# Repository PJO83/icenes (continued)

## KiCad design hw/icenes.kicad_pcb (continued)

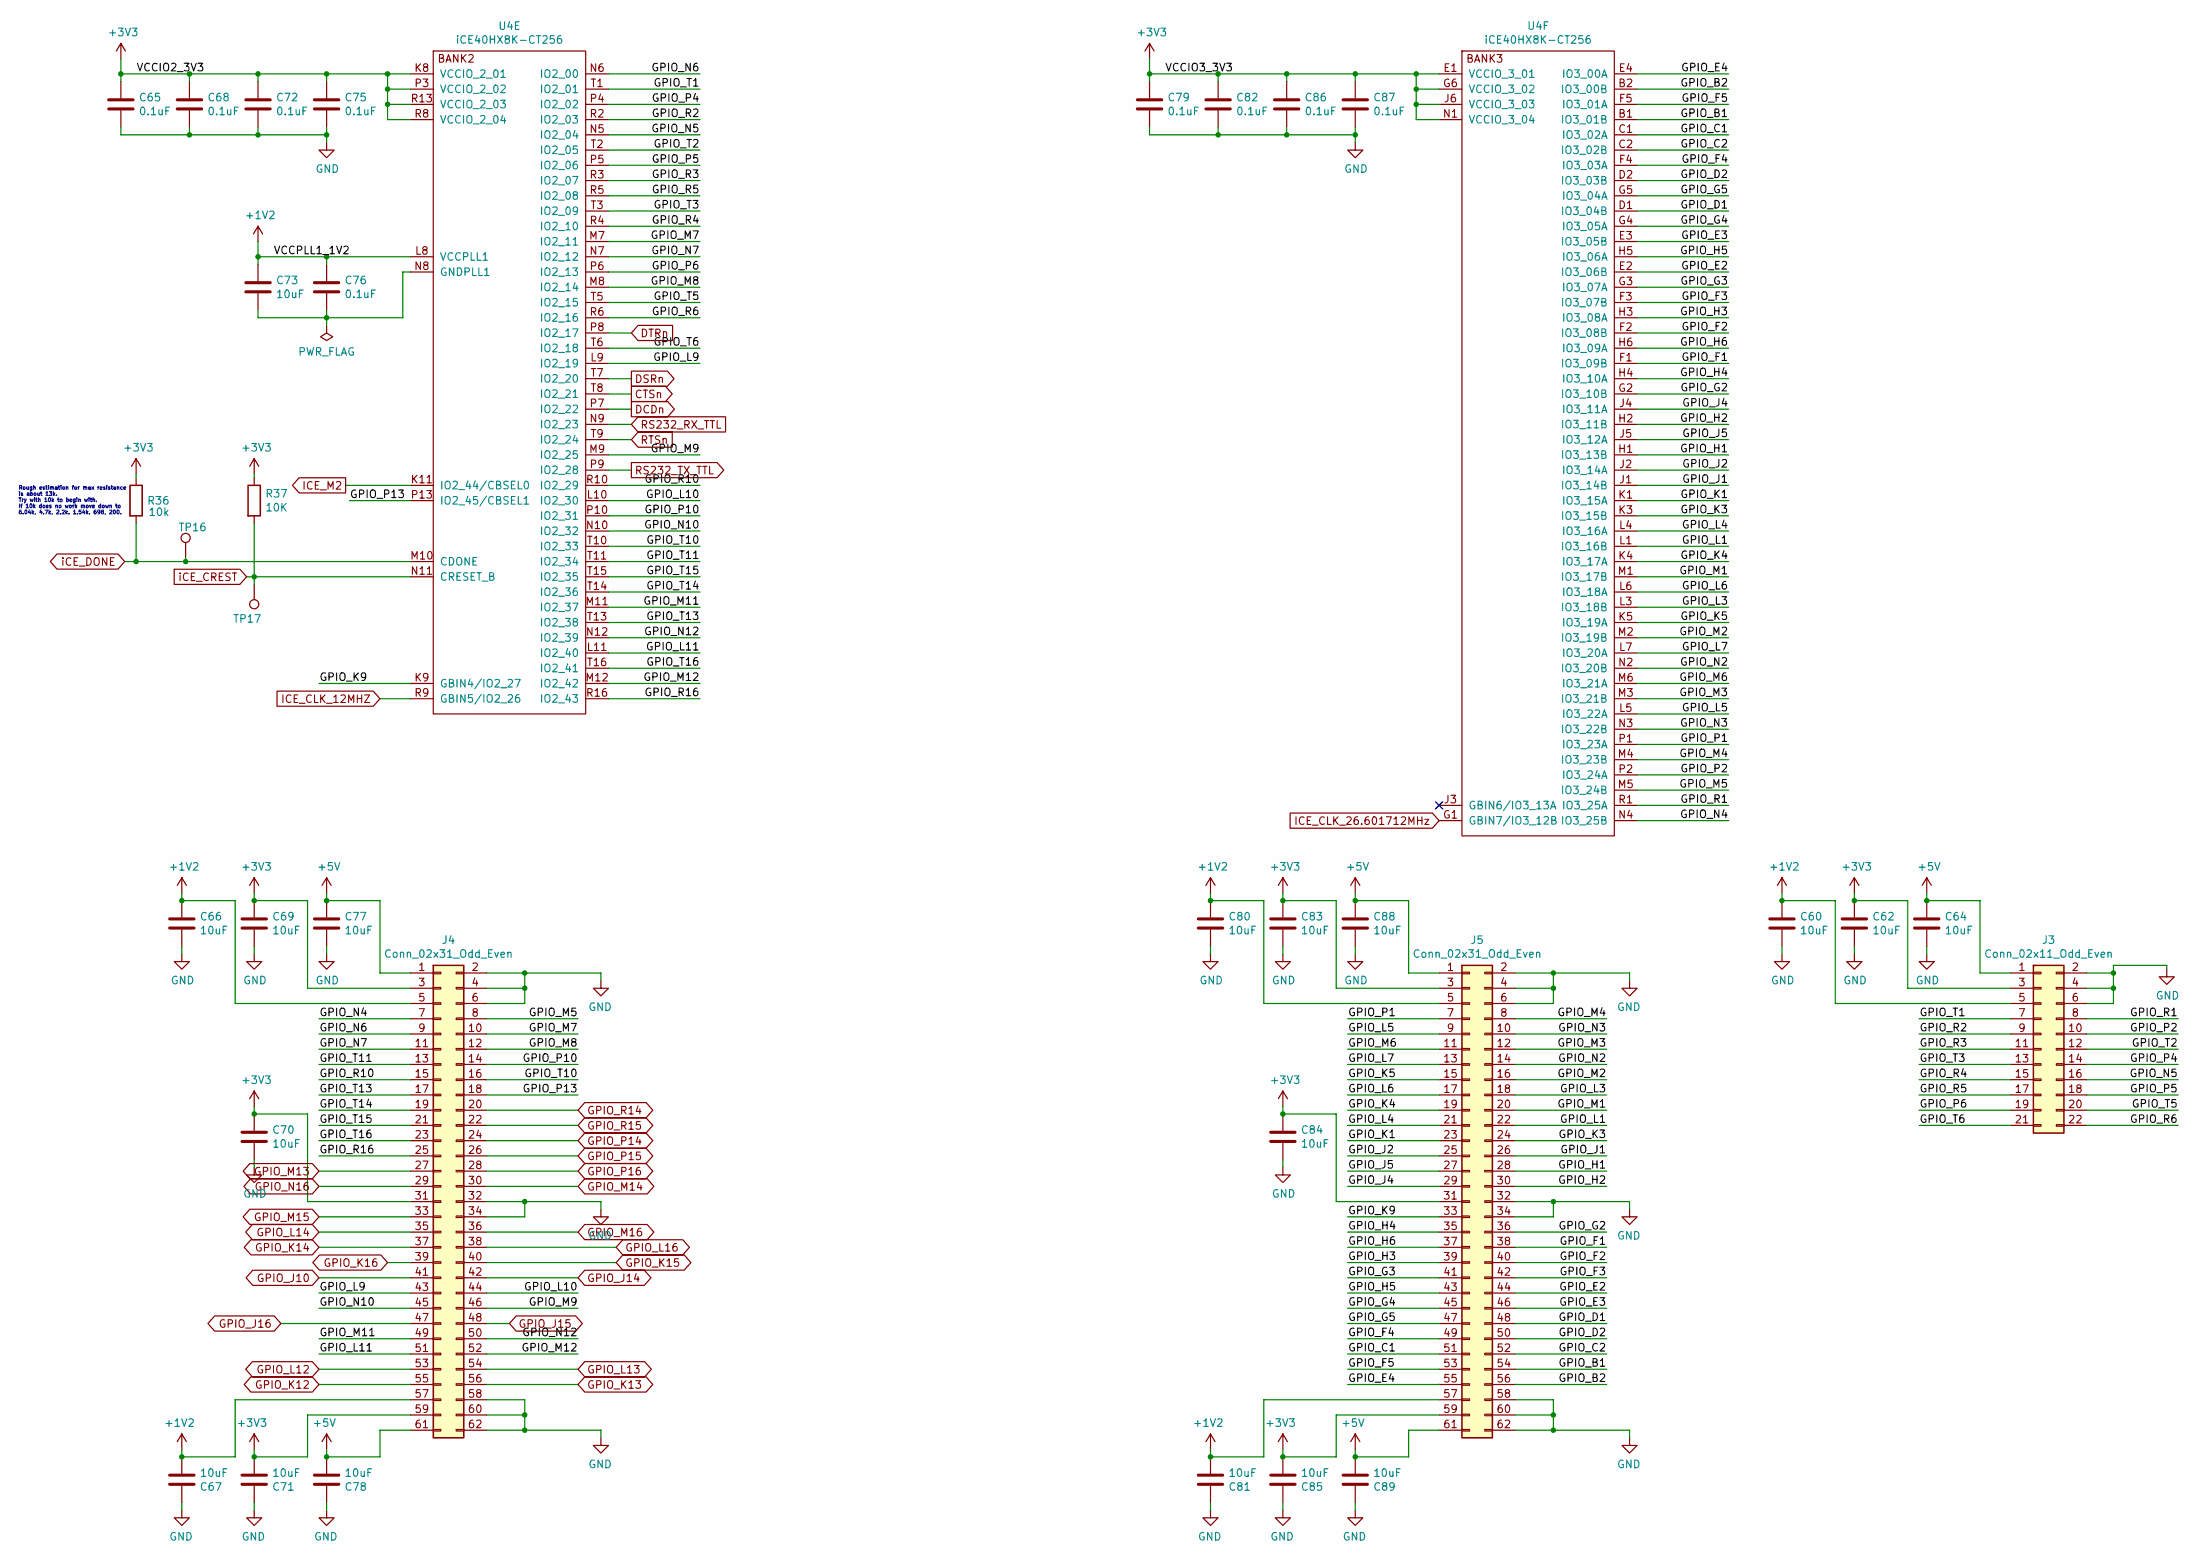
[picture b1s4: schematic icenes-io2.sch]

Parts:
C60, C62, C64, C66, C67, C69, C70, C71, C73, C77, C78, C80, C81, C83, C84, C85, C88, C89: C10uF; C_0603_1608Metric_Pad1.05x0.95mm_HandSolder; Part number GRM188R61A106KE69D
C65, C68, C72, C75, C76, C79, C82, C86, C87: C0.1uF; C_0603_1608Metric_Pad1.05x0.95mm_HandSolder; Part number 885012206020
J3: Conn_02x11_Odd_Even; PinSocket_2x11_P2.54mm_Vertical; Part number SSQ-111-02-T-D
J4, J5: Conn_02x31_Odd_Even; PinSocket_2x31_P2.54mm_Vertical; Part number 61306421821
R36, R37: R10K; R_0603_1608Metric_Pad1.05x0.95mm_HandSolder; Part number RC0603FR-0710KL
TP16, TP17: TestPoint; TestPoint_Pad_D1.0mm
U4: iCE40HX8K-CT256; BGA-256_14.0x14.0mm_Layout16x16_P0.8mm_Ball0.45mm_Pad0.32mm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; Part number iCE40HX8K-CT256

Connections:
+1V2: C60.1, C66.1, C67.2, C73.1, C76.1, C80.1, C81.2, J3.5, J4.5, J4.57, J5.5, J5.57, U4.L8 (VCCPLL1); also elsewhere on the board
+3V3: C62.1, C65.1, C68.1, C69.1, C70.1, C71.2, C72.1, C75.1, C79.1, C82.1, C83.1, C84.1, C85.2, C86.1, C87.1, J3.3, J4.3, J4.31, J4.59, J5.3, J5.31, J5.59, R36.1, R37.1, U4.E1 (VCCIO_3_01), U4.G6 (VCCIO_3_02), U4.J6 (VCCIO_3_03), U4.K8 (VCCIO_2_01), U4.N1 (VCCIO_3_04), U4.P3 (VCCIO_2_02), U4.R8 (VCCIO_2_04), U4.R13 (VCCIO_2_03); also elsewhere on the board
+5V: C64.1, C77.1, C78.2, C88.1, C89.2, J3.1, J4.1, J4.61, J5.1, J5.61; also elsewhere on the board
/ICENES io2/GPIO_B1: J5.54, U4.B1 (IO3_01B)
/ICENES io2/GPIO_B2: J5.56, U4.B2 (IO3_00B)
/ICENES io2/GPIO_C1: J5.51, U4.C1 (IO3_02A)
/ICENES io2/GPIO_C2: J5.52, U4.C2 (IO3_02B)
/ICENES io2/GPIO_D1: J5.48, U4.D1 (IO3_04B)
/ICENES io2/GPIO_D2: J5.50, U4.D2 (IO3_03B)
/ICENES io2/GPIO_E2: J5.44, U4.E2 (IO3_06B)
/ICENES io2/GPIO_E3: J5.46, U4.E3 (IO3_05B)
/ICENES io2/GPIO_E4: J5.55, U4.E4 (IO3_00A)
/ICENES io2/GPIO_F1: J5.38, U4.F1 (IO3_09B)
/ICENES io2/GPIO_F2: J5.40, U4.F2 (IO3_08B)
/ICENES io2/GPIO_F3: J5.42, U4.F3 (IO3_07B)
/ICENES io2/GPIO_F4: J5.49, U4.F4 (IO3_03A)
/ICENES io2/GPIO_F5: J5.53, U4.F5 (IO3_01A)
/ICENES io2/GPIO_G2: J5.36, U4.G2 (IO3_10B)
/ICENES io2/GPIO_G3: J5.41, U4.G3 (IO3_07A)
/ICENES io2/GPIO_G4: J5.45, U4.G4 (IO3_05A)
/ICENES io2/GPIO_G5: J5.47, U4.G5 (IO3_04A)
/ICENES io2/GPIO_H1: J5.28, U4.H1 (IO3_13B)
/ICENES io2/GPIO_H2: J5.30, U4.H2 (IO3_11B)
/ICENES io2/GPIO_H3: J5.39, U4.H3 (IO3_08A)
/ICENES io2/GPIO_H4: J5.35, U4.H4 (IO3_10A)
/ICENES io2/GPIO_H5: J5.43, U4.H5 (IO3_06A)
/ICENES io2/GPIO_H6: J5.37, U4.H6 (IO3_09A)
/ICENES io2/GPIO_J1: J5.26, U4.J1 (IO3_14B)
/ICENES io2/GPIO_J2: J5.25, U4.J2 (IO3_14A)
/ICENES io2/GPIO_J4: J5.29, U4.J4 (IO3_11A)
/ICENES io2/GPIO_J5: J5.27, U4.J5 (IO3_12A)
/ICENES io2/GPIO_K1: J5.23, U4.K1 (IO3_15A)
/ICENES io2/GPIO_K3: J5.24, U4.K3 (IO3_15B)
/ICENES io2/GPIO_K4: J5.19, U4.K4 (IO3_17A)
/ICENES io2/GPIO_K5: J5.15, U4.K5 (IO3_19A)
/ICENES io2/GPIO_K9: J5.33, U4.K9 (GBIN4/IO2_27)
/ICENES io2/GPIO_L1: J5.22, U4.L1 (IO3_16B)
/ICENES io2/GPIO_L3: J5.18, U4.L3 (IO3_18B)
/ICENES io2/GPIO_L4: J5.21, U4.L4 (IO3_16A)
/ICENES io2/GPIO_L5: J5.9, U4.L5 (IO3_22A)
/ICENES io2/GPIO_L6: J5.17, U4.L6 (IO3_18A)
/ICENES io2/GPIO_L7: J5.13, U4.L7 (IO3_20A)
/ICENES io2/GPIO_L9: J4.43, U4.L9 (IO2_19)
/ICENES io2/GPIO_L10: J4.44, U4.L10 (IO2_30)
/ICENES io2/GPIO_L11: J4.51, U4.L11 (IO2_40)
/ICENES io2/GPIO_M1: J5.20, U4.M1 (IO3_17B)
/ICENES io2/GPIO_M2: J5.16, U4.M2 (IO3_19B)
/ICENES io2/GPIO_M3: J5.12, U4.M3 (IO3_21B)
/ICENES io2/GPIO_M4: J5.8, U4.M4 (IO3_23B)
/ICENES io2/GPIO_M5: J4.8, U4.M5 (IO3_24B)
/ICENES io2/GPIO_M6: J5.11, U4.M6 (IO3_21A)
/ICENES io2/GPIO_M7: J4.10, U4.M7 (IO2_11)
/ICENES io2/GPIO_M8: J4.12, U4.M8 (IO2_14)
/ICENES io2/GPIO_M9: J4.46, U4.M9 (IO2_25)
/ICENES io2/GPIO_M11: J4.49, U4.M11 (IO2_37)
/ICENES io2/GPIO_M12: J4.52, U4.M12 (IO2_42)
/ICENES io2/GPIO_N2: J5.14, U4.N2 (IO3_20B)
/ICENES io2/GPIO_N3: J5.10, U4.N3 (IO3_22B)
/ICENES io2/GPIO_N4: J4.7, U4.N4 (IO3_25B)
/ICENES io2/GPIO_N5: J3.16, U4.N5 (IO2_04)
/ICENES io2/GPIO_N6: J4.9, U4.N6 (IO2_00)
/ICENES io2/GPIO_N7: J4.11, U4.N7 (IO2_12)
/ICENES io2/GPIO_N10: J4.45, U4.N10 (IO2_32)
/ICENES io2/GPIO_N12: J4.50, U4.N12 (IO2_39)
/ICENES io2/GPIO_P1: J5.7, U4.P1 (IO3_23A)
/ICENES io2/GPIO_P2: J3.10, U4.P2 (IO3_24A)
/ICENES io2/GPIO_P4: J3.14, U4.P4 (IO2_02)
/ICENES io2/GPIO_P5: J3.18, U4.P5 (IO2_06)
/ICENES io2/GPIO_P6: J3.19, U4.P6 (IO2_13)
/ICENES io2/GPIO_P10: J4.14, U4.P10 (IO2_31)
/ICENES io2/GPIO_P13: J4.18, U4.P13 (IO2_45/CBSEL1)
/ICENES io2/GPIO_R1: J3.8, U4.R1 (IO3_25A)
/ICENES io2/GPIO_R2: J3.9, U4.R2 (IO2_03)
/ICENES io2/GPIO_R3: J3.11, U4.R3 (IO2_07)
/ICENES io2/GPIO_R4: J3.15, U4.R4 (IO2_10)
/ICENES io2/GPIO_R5: J3.17, U4.R5 (IO2_08)
/ICENES io2/GPIO_R6: J3.22, U4.R6 (IO2_16)
/ICENES io2/GPIO_R10: J4.15, U4.R10 (IO2_29)
/ICENES io2/GPIO_R16: J4.25, U4.R16 (IO2_43)
/ICENES io2/GPIO_T1: J3.7, U4.T1 (IO2_01)
/ICENES io2/GPIO_T2: J3.12, U4.T2 (IO2_05)
/ICENES io2/GPIO_T3: J3.13, U4.T3 (IO2_09)
/ICENES io2/GPIO_T5: J3.20, U4.T5 (IO2_15)
/ICENES io2/GPIO_T6: J3.21, U4.T6 (IO2_18)
/ICENES io2/GPIO_T10: J4.16, U4.T10 (IO2_33)
/ICENES io2/GPIO_T11: J4.13, U4.T11 (IO2_34)
/ICENES io2/GPIO_T13: J4.17, U4.T13 (IO2_38)
/ICENES io2/GPIO_T14: J4.19, U4.T14 (IO2_36)
/ICENES io2/GPIO_T15: J4.21, U4.T15 (IO2_35)
/ICENES io2/GPIO_T16: J4.23, U4.T16 (IO2_41)
CTSn: U4.T8 (IO2_21); also elsewhere on the board
DCDn: U4.P7 (IO2_22); also elsewhere on the board
DSRn: U4.T7 (IO2_20); also elsewhere on the board
DTRn: U4.P8 (IO2_17); also elsewhere on the board
GND: C60.2, C62.2, C64.2, C65.2, C66.2, C67.1, C68.2, C69.2, C70.2, C71.1, C72.2, C75.2, C77.2, C78.1, C79.2, C80.2, C81.1, C82.2, C83.2, C84.2, C85.1, C86.2, C87.2, C88.2, C89.1, J3.2, J3.4, J3.6, J4.2, J4.4, J4.6, J4.32, J4.34, J4.58, J4.60, J4.62, J5.2, J5.4, J5.6, J5.32, J5.34, J5.58, J5.60, J5.62; also elsewhere on the board
GPIO_J10: J4.41; also elsewhere on the board
GPIO_J14: J4.42; also elsewhere on the board
GPIO_J15: J4.48; also elsewhere on the board
GPIO_J16: J4.47; also elsewhere on the board
GPIO_K12: J4.55; also elsewhere on the board
GPIO_K13: J4.56; also elsewhere on the board
GPIO_K14: J4.37; also elsewhere on the board
GPIO_K15: J4.40; also elsewhere on the board
GPIO_K16: J4.39; also elsewhere on the board
GPIO_L12: J4.53; also elsewhere on the board
GPIO_L13: J4.54; also elsewhere on the board
GPIO_L14: J4.35; also elsewhere on the board
GPIO_L16: J4.38; also elsewhere on the board
GPIO_M13: J4.27; also elsewhere on the board
GPIO_M14: J4.30; also elsewhere on the board
GPIO_M15: J4.33; also elsewhere on the board
GPIO_M16: J4.36; also elsewhere on the board
GPIO_N16: J4.29; also elsewhere on the board
GPIO_P14: J4.24; also elsewhere on the board
GPIO_P15: J4.26; also elsewhere on the board
GPIO_P16: J4.28; also elsewhere on the board
GPIO_R14: J4.20; also elsewhere on the board
GPIO_R15: J4.22; also elsewhere on the board
ICE_CLK_12MHZ: U4.R9 (GBIN5/IO2_26); also elsewhere on the board
ICE_CLK_26.601712MHz: U4.G1 (GBIN7/IO3_12B); also elsewhere on the board
ICE_M2: U4.K11 (IO2_44/CBSEL0); also elsewhere on the board
unnamed: C73.2, C76.2, U4.N8 (GNDPLL1)
RS232_RX_TTL: U4.N9 (IO2_23); also elsewhere on the board
RS232_TX_TTL: U4.P9 (IO2_28); also elsewhere on the board
RTSn: U4.T9 (IO2_24); also elsewhere on the board
iCE_CREST: R37.2, TP17.1, U4.N11 (CRESET_B); also elsewhere on the board
iCE_DONE: R36.2, TP16.1, U4.M10 (CDONE); also elsewhere on the board

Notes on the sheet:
Rough estimation for max resistance is about 13k. Try with 10k to begin with. If 10k does no work move down to 6.04k, 4.7k, 2.2k. 1.54k. 698, 200.

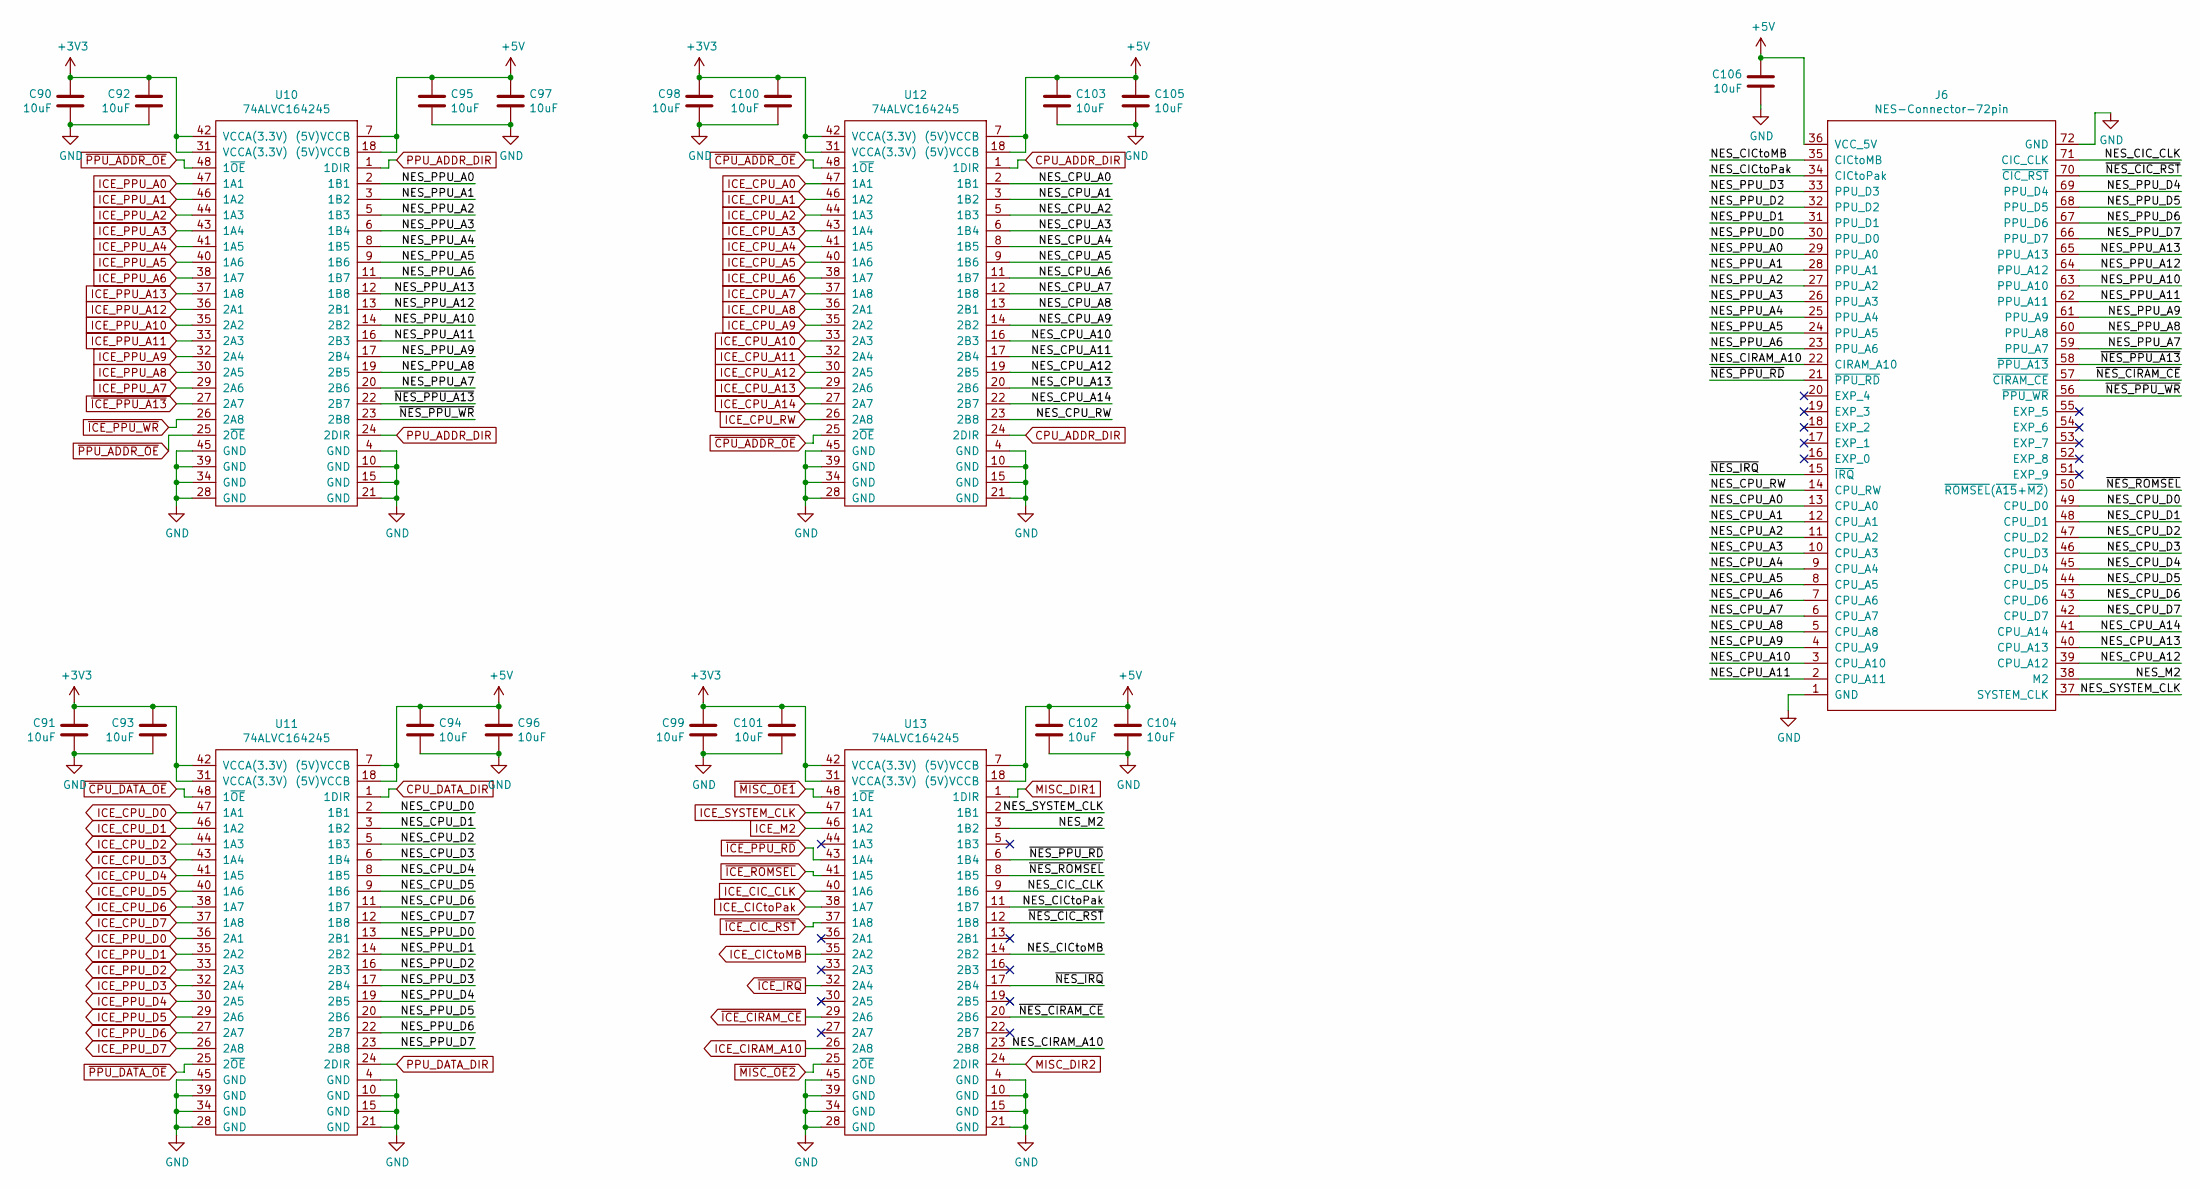
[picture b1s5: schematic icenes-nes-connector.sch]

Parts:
C90, C91, C92, C93, C94, C95, C96, C97, C98, C99, C100, C101, C102, C103, C104, C105, C106: C10uF; C_0603_1608Metric_Pad1.05x0.95mm_HandSolder; Part number GRM188R61A106KE69D
J6: NES-Connector-72pin; DIP-72-NES-CONNECTOR
U10, U11, U12, U13: 74ALVC164245; TSSOP-48_6.1x12.5mm_P0.5mm; Part number 74ALVC164245PAG8

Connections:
+3V3: C90.2, C91.2, C92.2, C93.2, C98.2, C99.2, C100.2, C101.2, U10.31 (VCCA(3.3V)), U10.42 (VCCA(3.3V)), U11.31 (VCCA(3.3V)), U11.42 (VCCA(3.3V)), U12.31 (VCCA(3.3V)), U12.42 (VCCA(3.3V)), U13.31 (VCCA(3.3V)), U13.42 (VCCA(3.3V)); also elsewhere on the board
+5V: C94.1, C95.1, C96.1, C97.1, C102.1, C103.1, C104.1, C105.1, C106.2, J6.36 (VCC_5V), U10.7 ((5V)VCCB), U10.18 ((5V)VCCB), U11.7 ((5V)VCCB), U11.18 ((5V)VCCB), U12.7 ((5V)VCCB), U12.18 ((5V)VCCB), U13.7 ((5V)VCCB), U13.18 ((5V)VCCB); also elsewhere on the board
/ICENES NES Connector/NES_CIC_CLK: J6.71 (CIC_CLK), U13.9 (1B6)
/ICENES NES Connector/NES_CICtoMB: J6.35 (CICtoMB), U13.14 (2B2)
/ICENES NES Connector/NES_CICtoPak: J6.34 (CICtoPak), U13.11 (1B7)
/ICENES NES Connector/NES_CIRAM_A10: J6.22 (CIRAM_A10), U13.23 (2B8)
/ICENES NES Connector/NES_CPU_A0: J6.13 (CPU_A0), U12.2 (1B1)
/ICENES NES Connector/NES_CPU_A1: J6.12 (CPU_A1), U12.3 (1B2)
/ICENES NES Connector/NES_CPU_A2: J6.11 (CPU_A2), U12.5 (1B3)
/ICENES NES Connector/NES_CPU_A3: J6.10 (CPU_A3), U12.6 (1B4)
/ICENES NES Connector/NES_CPU_A4: J6.9 (CPU_A4), U12.8 (1B5)
/ICENES NES Connector/NES_CPU_A5: J6.8 (CPU_A5), U12.9 (1B6)
/ICENES NES Connector/NES_CPU_A6: J6.7 (CPU_A6), U12.11 (1B7)
/ICENES NES Connector/NES_CPU_A7: J6.6 (CPU_A7), U12.12 (1B8)
/ICENES NES Connector/NES_CPU_A8: J6.5 (CPU_A8), U12.13 (2B1)
/ICENES NES Connector/NES_CPU_A9: J6.4 (CPU_A9), U12.14 (2B2)
/ICENES NES Connector/NES_CPU_A10: J6.3 (CPU_A10), U12.16 (2B3)
/ICENES NES Connector/NES_CPU_A11: J6.2 (CPU_A11), U12.17 (2B4)
/ICENES NES Connector/NES_CPU_A12: J6.39 (CPU_A12), U12.19 (2B5)
/ICENES NES Connector/NES_CPU_A13: J6.40 (CPU_A13), U12.20 (2B6)
/ICENES NES Connector/NES_CPU_A14: J6.41 (CPU_A14), U12.22 (2B7)
/ICENES NES Connector/NES_CPU_D0: J6.49 (CPU_D0), U11.2 (1B1)
/ICENES NES Connector/NES_CPU_D1: J6.48 (CPU_D1), U11.3 (1B2)
/ICENES NES Connector/NES_CPU_D2: J6.47 (CPU_D2), U11.5 (1B3)
/ICENES NES Connector/NES_CPU_D3: J6.46 (CPU_D3), U11.6 (1B4)
/ICENES NES Connector/NES_CPU_D4: J6.45 (CPU_D4), U11.8 (1B5)
/ICENES NES Connector/NES_CPU_D5: J6.44 (CPU_D5), U11.9 (1B6)
/ICENES NES Connector/NES_CPU_D6: J6.43 (CPU_D6), U11.11 (1B7)
/ICENES NES Connector/NES_CPU_D7: J6.42 (CPU_D7), U11.12 (1B8)
/ICENES NES Connector/NES_CPU_RW: J6.14 (CPU_RW), U12.23 (2B8)
/ICENES NES Connector/NES_M2: J6.38 (M2), U13.3 (1B2)
/ICENES NES Connector/NES_PPU_A0: J6.29 (PPU_A0), U10.2 (1B1)
/ICENES NES Connector/NES_PPU_A1: J6.28 (PPU_A1), U10.3 (1B2)
/ICENES NES Connector/NES_PPU_A2: J6.27 (PPU_A2), U10.5 (1B3)
/ICENES NES Connector/NES_PPU_A3: J6.26 (PPU_A3), U10.6 (1B4)
/ICENES NES Connector/NES_PPU_A4: J6.25 (PPU_A4), U10.8 (1B5)
/ICENES NES Connector/NES_PPU_A5: J6.24 (PPU_A5), U10.9 (1B6)
/ICENES NES Connector/NES_PPU_A6: J6.23 (PPU_A6), U10.11 (1B7)
/ICENES NES Connector/NES_PPU_A7: J6.59 (PPU_A7), U10.20 (2B6)
/ICENES NES Connector/NES_PPU_A8: J6.60 (PPU_A8), U10.19 (2B5)
/ICENES NES Connector/NES_PPU_A9: J6.61 (PPU_A9), U10.17 (2B4)
/ICENES NES Connector/NES_PPU_A10: J6.63 (PPU_A10), U10.14 (2B2)
/ICENES NES Connector/NES_PPU_A11: J6.62 (PPU_A11), U10.16 (2B3)
/ICENES NES Connector/NES_PPU_A12: J6.64 (PPU_A12), U10.13 (2B1)
/ICENES NES Connector/NES_PPU_A13: J6.65 (PPU_A13), U10.12 (1B8)
/ICENES NES Connector/NES_PPU_D0: J6.30 (PPU_D0), U11.13 (2B1)
/ICENES NES Connector/NES_PPU_D1: J6.31 (PPU_D1), U11.14 (2B2)
/ICENES NES Connector/NES_PPU_D2: J6.32 (PPU_D2), U11.16 (2B3)
/ICENES NES Connector/NES_PPU_D3: J6.33 (PPU_D3), U11.17 (2B4)
/ICENES NES Connector/NES_PPU_D4: J6.69 (PPU_D4), U11.19 (2B5)
/ICENES NES Connector/NES_PPU_D5: J6.68 (PPU_D5), U11.20 (2B6)
/ICENES NES Connector/NES_PPU_D6: J6.67 (PPU_D6), U11.22 (2B7)
/ICENES NES Connector/NES_PPU_D7: J6.66 (PPU_D7), U11.23 (2B8)
/ICENES NES Connector/NES_SYSTEM_CLK: J6.37 (SYSTEM_CLK), U13.2 (1B1)
/ICENES NES Connector/~NES_CIC_RST: J6.70 (~CIC_RST), U13.12 (1B8)
/ICENES NES Connector/~NES_CIRAM_CE: J6.57 (~CIRAM_CE), U13.20 (2B6)
/ICENES NES Connector/~NES_IRQ: J6.15 (~IRQ), U13.17 (2B4)
/ICENES NES Connector/~NES_PPU_A13: J6.58 (~PPU_A13), U10.22 (2B7)
/ICENES NES Connector/~NES_PPU_RD: J6.21 (~PPU_RD), U13.6 (1B4)
/ICENES NES Connector/~NES_PPU_WR: J6.56 (~PPU_WR), U10.23 (2B8)
/ICENES NES Connector/~NES_ROMSEL: J6.50 (~ROMSEL~(~A15~+~M2~)), U13.8 (1B5)
CPU_ADDR_DIR: U12.1 (1DIR), U12.24 (2DIR); also elsewhere on the board
CPU_DATA_DIR: U11.1 (1DIR); also elsewhere on the board
GND: C90.1, C91.1, C92.1, C93.1, C94.2, C95.2, C96.2, C97.2, C98.1, C99.1, C100.1, C101.1, C102.2, C103.2, C104.2, C105.2, C106.1, J6.1 (GND), J6.72 (GND), U10.4 (GND), U10.10 (GND), U10.15 (GND), U10.21 (GND), U10.28 (GND), U10.34 (GND), U10.39 (GND), U10.45 (GND), U11.4 (GND), U11.10 (GND), U11.15 (GND), U11.21 (GND), U11.28 (GND), U11.34 (GND), U11.39 (GND), U11.45 (GND), U12.4 (GND), U12.10 (GND), U12.15 (GND), U12.21 (GND), U12.28 (GND), U12.34 (GND), U12.39 (GND), U12.45 (GND), U13.4 (GND), U13.10 (GND), U13.15 (GND), U13.21 (GND), U13.28 (GND), U13.34 (GND), U13.39 (GND), U13.45 (GND); also elsewhere on the board
ICE_CIC_CLK: U13.40 (1A6); also elsewhere on the board
ICE_CICtoMB: U13.35 (2A2); also elsewhere on the board
ICE_CICtoPak: U13.38 (1A7); also elsewhere on the board
ICE_CIRAM_A10: U13.26 (2A8); also elsewhere on the board
ICE_CPU_A0: U12.47 (1A1); also elsewhere on the board
ICE_CPU_A1: U12.46 (1A2); also elsewhere on the board
ICE_CPU_A2: U12.44 (1A3); also elsewhere on the board
ICE_CPU_A3: U12.43 (1A4); also elsewhere on the board
ICE_CPU_A4: U12.41 (1A5); also elsewhere on the board
ICE_CPU_A5: U12.40 (1A6); also elsewhere on the board
ICE_CPU_A6: U12.38 (1A7); also elsewhere on the board
ICE_CPU_A7: U12.37 (1A8); also elsewhere on the board
ICE_CPU_A8: U12.36 (2A1); also elsewhere on the board
ICE_CPU_A9: U12.35 (2A2); also elsewhere on the board
ICE_CPU_A10: U12.33 (2A3); also elsewhere on the board
ICE_CPU_A11: U12.32 (2A4); also elsewhere on the board
ICE_CPU_A12: U12.30 (2A5); also elsewhere on the board
ICE_CPU_A13: U12.29 (2A6); also elsewhere on the board
ICE_CPU_A14: U12.27 (2A7); also elsewhere on the board
ICE_CPU_D0: U11.47 (1A1); also elsewhere on the board
ICE_CPU_D1: U11.46 (1A2); also elsewhere on the board
ICE_CPU_D2: U11.44 (1A3); also elsewhere on the board
ICE_CPU_D3: U11.43 (1A4); also elsewhere on the board
ICE_CPU_D4: U11.41 (1A5); also elsewhere on the board
ICE_CPU_D5: U11.40 (1A6); also elsewhere on the board
ICE_CPU_D6: U11.38 (1A7); also elsewhere on the board
ICE_CPU_D7: U11.37 (1A8); also elsewhere on the board
ICE_CPU_RW: U12.26 (2A8); also elsewhere on the board
ICE_M2: U13.46 (1A2); also elsewhere on the board
ICE_PPU_A0: U10.47 (1A1); also elsewhere on the board
ICE_PPU_A1: U10.46 (1A2); also elsewhere on the board
ICE_PPU_A2: U10.44 (1A3); also elsewhere on the board
ICE_PPU_A3: U10.43 (1A4); also elsewhere on the board
ICE_PPU_A4: U10.41 (1A5); also elsewhere on the board
ICE_PPU_A5: U10.40 (1A6); also elsewhere on the board
ICE_PPU_A6: U10.38 (1A7); also elsewhere on the board
ICE_PPU_A7: U10.29 (2A6); also elsewhere on the board
ICE_PPU_A8: U10.30 (2A5); also elsewhere on the board
ICE_PPU_A9: U10.32 (2A4); also elsewhere on the board
ICE_PPU_A10: U10.35 (2A2); also elsewhere on the board
ICE_PPU_A11: U10.33 (2A3); also elsewhere on the board
ICE_PPU_A12: U10.36 (2A1); also elsewhere on the board
ICE_PPU_A13: U10.37 (1A8); also elsewhere on the board
ICE_PPU_D0: U11.36 (2A1); also elsewhere on the board
ICE_PPU_D1: U11.35 (2A2); also elsewhere on the board
ICE_PPU_D2: U11.33 (2A3); also elsewhere on the board
ICE_PPU_D3: U11.32 (2A4); also elsewhere on the board
ICE_PPU_D4: U11.30 (2A5); also elsewhere on the board
ICE_PPU_D5: U11.29 (2A6); also elsewhere on the board
ICE_PPU_D6: U11.27 (2A7); also elsewhere on the board
ICE_PPU_D7: U11.26 (2A8); also elsewhere on the board
ICE_SYSTEM_CLK: U13.47 (1A1); also elsewhere on the board
MISC_DIR1: U13.1 (1DIR); also elsewhere on the board
MISC_DIR2: U13.24 (2DIR); also elsewhere on the board
PPU_ADDR_DIR: U10.1 (1DIR), U10.24 (2DIR); also elsewhere on the board
PPU_DATA_DIR: U11.24 (2DIR); also elsewhere on the board
~CPU_ADDR_OE: U12.25 (2~OE), U12.48 (1~OE); also elsewhere on the board
~CPU_DATA_OE: U11.48 (1~OE); also elsewhere on the board
~ICE_CIC_RST: U13.37 (1A8); also elsewhere on the board
~ICE_CIRAM_CE: U13.29 (2A6); also elsewhere on the board
~ICE_IRQ: U13.32 (2A4); also elsewhere on the board
~ICE_PPU_A13: U10.27 (2A7); also elsewhere on the board
~ICE_PPU_RD: U13.43 (1A4); also elsewhere on the board
~ICE_PPU_WR: U10.26 (2A8); also elsewhere on the board
~ICE_ROMSEL: U13.41 (1A5); also elsewhere on the board
~MISC_OE1: U13.48 (1~OE); also elsewhere on the board
~MISC_OE2: U13.25 (2~OE); also elsewhere on the board
~PPU_ADDR_OE: U10.25 (2~OE), U10.48 (1~OE); also elsewhere on the board
~PPU_DATA_OE: U11.25 (2~OE); also elsewhere on the board

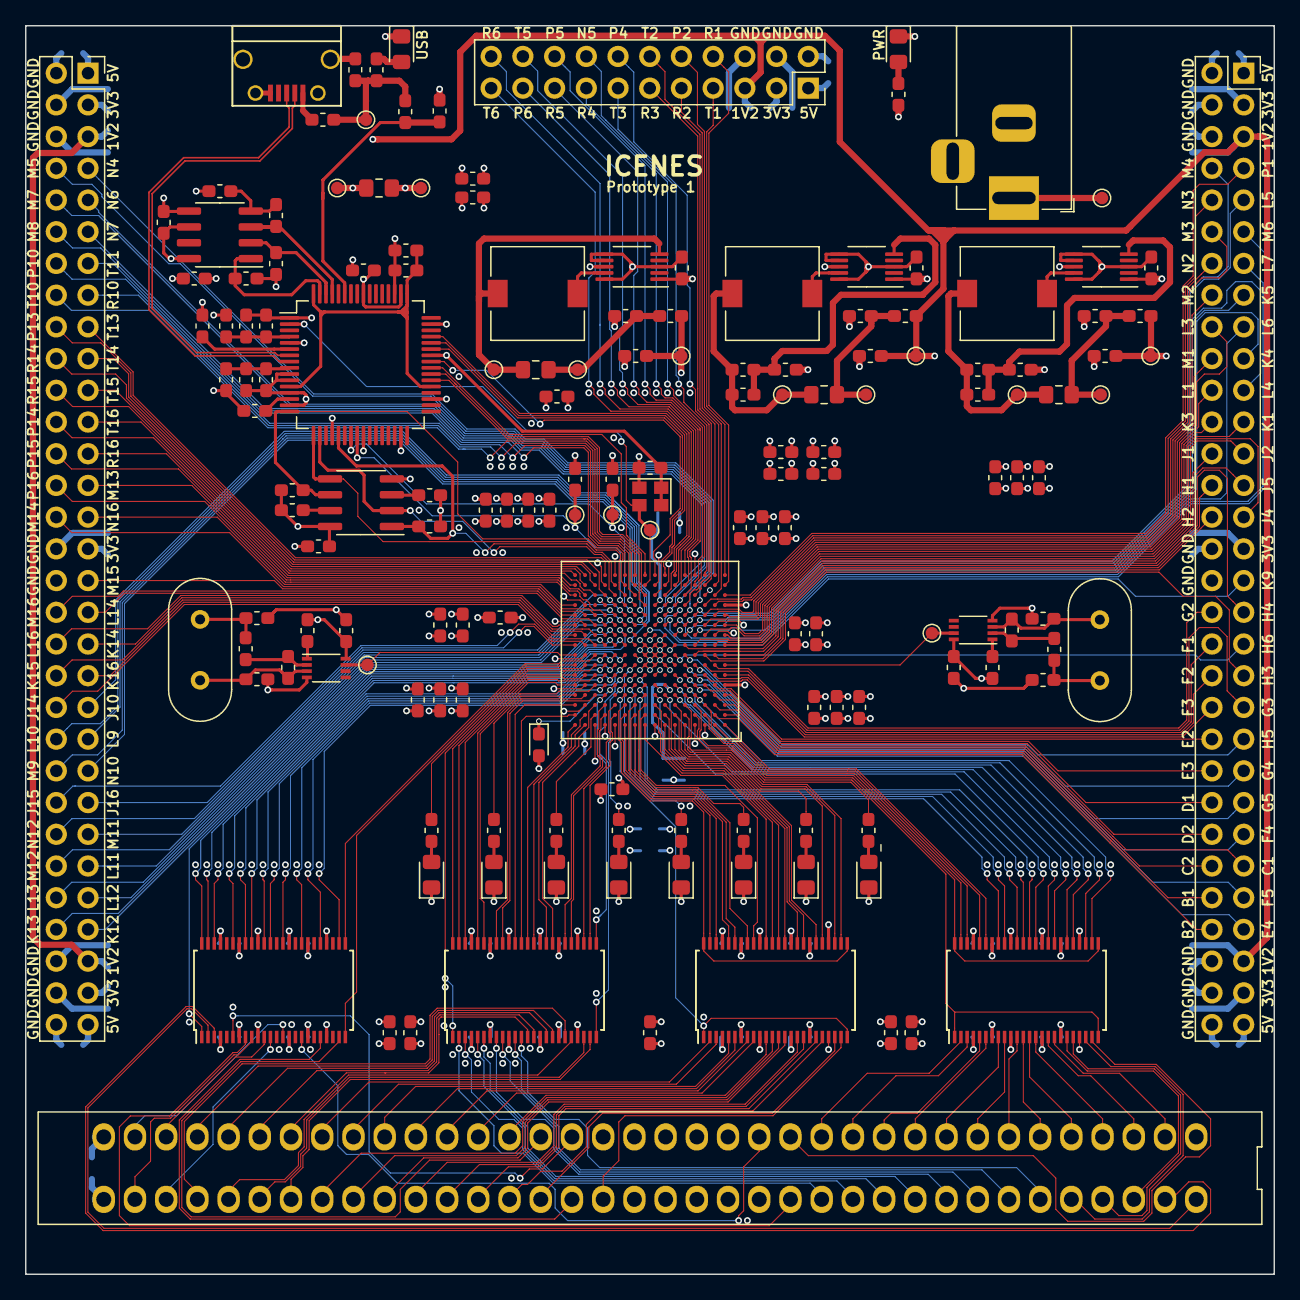
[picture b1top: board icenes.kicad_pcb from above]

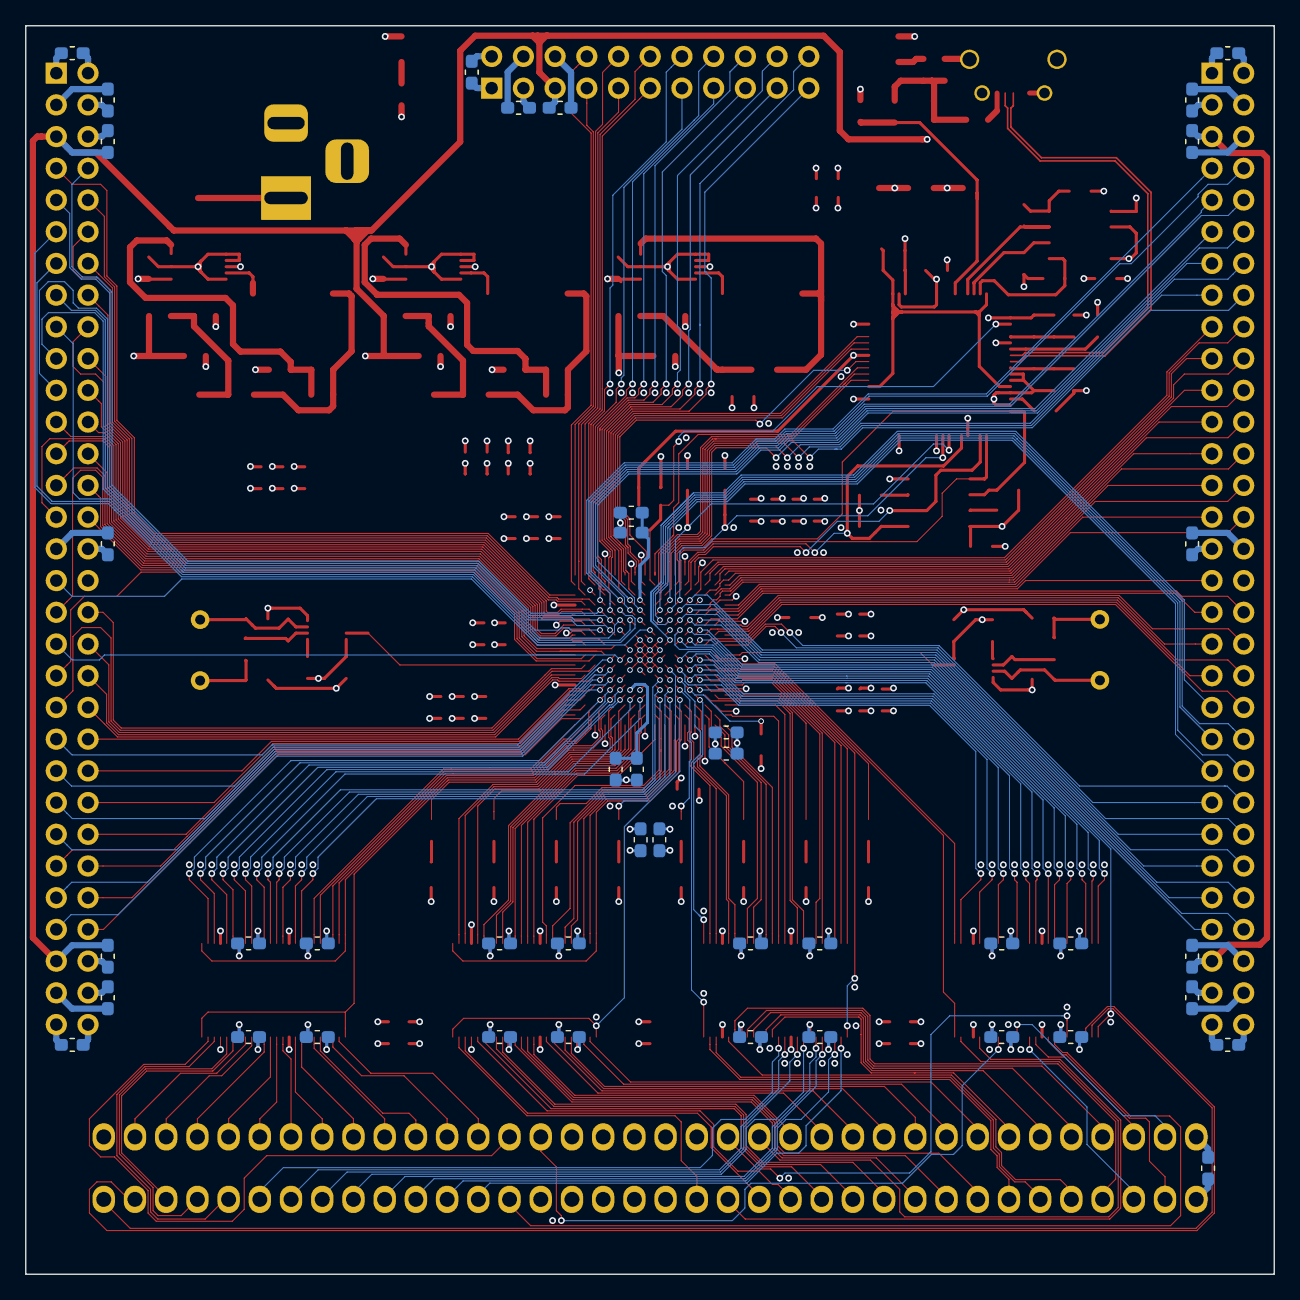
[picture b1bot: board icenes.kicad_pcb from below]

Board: 6 copper layers, 100.0 x 100.0 mm, 203 parts (42 on the bottom side), 318 nets.

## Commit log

2019-07-01 Initial commit.
2019-07-01 Moved files to hw fodler.
2019-07-01 Removed unused files and updated name in license.
2019-07-27 Added voltage generators for 3.3V, 1.2V and 5V. Added more info and footprints to some components. Connected signals to the NES connector to banks 0 and 1.
2019-07-28 Added 8 LED. Added GPIO header for the rest of the GPIO pins on bank1. Labeled all GPIO pins.
2019-07-28 Removed unused footprint lib.
2019-07-29 GPIO headers for banks 2 and 3.
2019-07-31 Footprints.
2019-08-25 Completed USB interface. Clock sources for PAL and NTSC frequencies. Added a 133MHz clock (max input to PLL). Some more stuff.
2019-08-26 Added missing footprints.
2019-08-27 Minor fixes.
2019-08-27 Fixed all ECR warnings.
2019-08-27 Fixed wrong inductor choice.
2019-08-27 Removed test points from power good signals.
2019-08-27 Added voltage range in Vin lable (+5V to +10V).
2019-08-27 Changed inductor.
2019-08-28 Added missing footprint for the new inductor. Added 3d models to the barrel jack and oscillators.
2019-08-28 Connected the chip select pin of the SPI flash to FT2232H and to the FPGA.
2019-08-30 Datasheets.
2019-08-31 Fixed incorrect reference between USB_VBUS and +3V3_FTDI
2019-09-01 Rough board layout.
2019-09-04 layout work.
2019-09-08 Layout.
2019-09-28 Layout. Added some info for the PAL crystal.
2019-10-16 Layout. - Changed footprint of the nes connector from 2.54mm pitch and 5.08mm row pitch to 2.5mm pitch and 0.5mm row pitch.
2019-10-18 Layout. Cleaned up nes connector footprints. Adjusted LED (D1) series resistor. Adjusted the voltage divider to BCBUS7 on FT2232H. Set pull up resistor to CDONE to 10k.
2019-10-22 Added pwr led.
